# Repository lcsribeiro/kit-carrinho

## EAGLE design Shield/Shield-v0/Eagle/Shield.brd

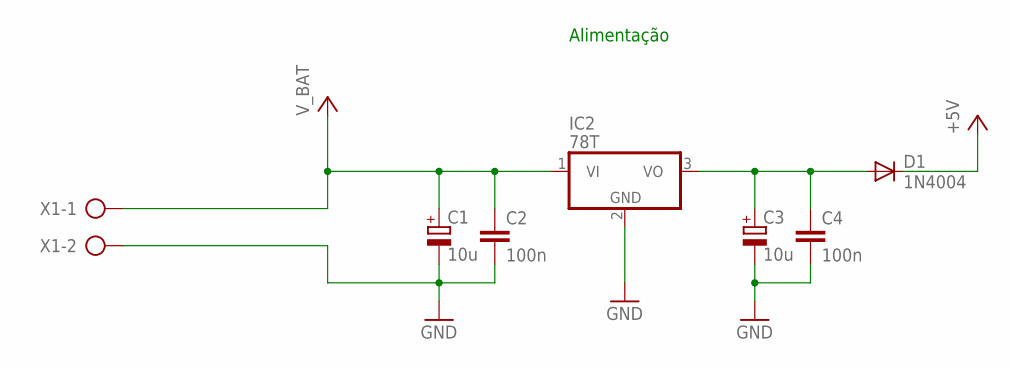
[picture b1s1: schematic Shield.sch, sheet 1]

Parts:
C1, C3: 10u; E2,5-5
C2, C4: 100n; C025-024X044
D1: 1N4004; DO41-10
IC2: 78T; TO220H
X1: AK300/2

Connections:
+5: C3.+, C4.1, D1.A, IC2.3 (VO)
+5V: D1.C; also elsewhere on the board
GND: C1.-, C2.2, C3.-, C4.2, IC2.2 (GND), X1.2; also elsewhere on the board
V_BAT: C1.+, C2.1, IC2.1 (VI), X1.1; also elsewhere on the board

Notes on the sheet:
Alimentação

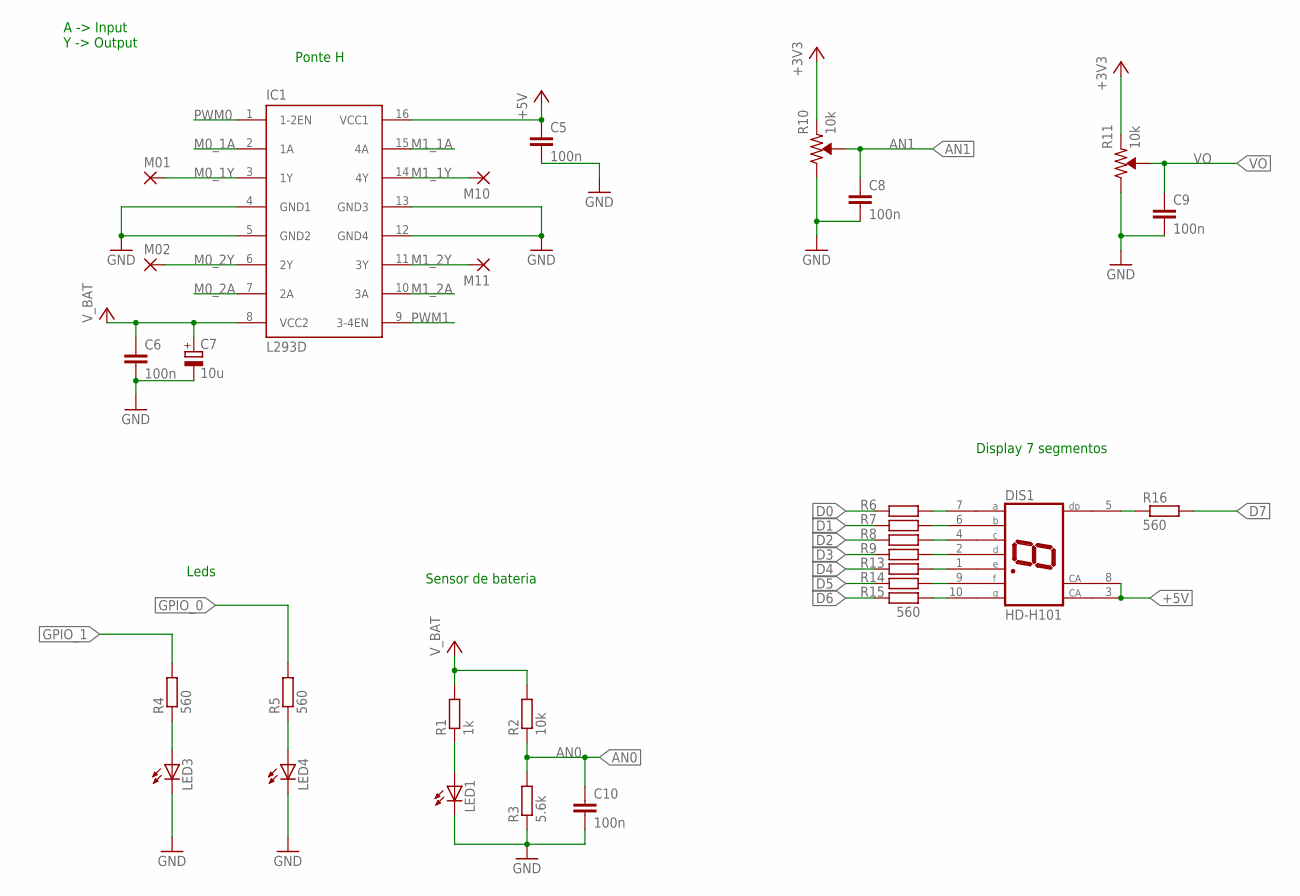
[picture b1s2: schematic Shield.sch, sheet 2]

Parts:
C5, C6, C8, C9, C10: 100n; C025-024X044
C7: 10u; E2,5-5
DIS1: HD-H101; HDSP-M
IC1: L293D; DIL16
LED1, LED3, LED4: LED5MM
M01, M02, M10, M11: 2,54/1,1
R1: 1k; 0204/7
R2: 10k; 0204/7
R3: 5.6k; 0204/7
R4, R5, R6, R7, R8, R9, R13, R14, R15, R16: 560; 0204/7
R10, R11: 10k; TRIMPOT-PTH-3386U

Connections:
+3V3: R10.1 (CCW), R11.1 (CCW); also elsewhere on the board
+5V: C5.1, DIS1.3 (CA), DIS1.8 (CA), IC1.16 (VCC1); also elsewhere on the board
AN0: C10.1, R2.1, R3.2; also elsewhere on the board
AN1: C8.1, R10.2 (WIPER); also elsewhere on the board
D0: R6.1; also elsewhere on the board
D1: R7.1; also elsewhere on the board
D2: R8.1; also elsewhere on the board
D3: R9.1; also elsewhere on the board
D4: R13.1; also elsewhere on the board
D5: R14.1; also elsewhere on the board
D6: R15.1; also elsewhere on the board
D7: R16.2; also elsewhere on the board
GND: C5.2, C6.2, C7.-, C8.2, C9.2, C10.2, IC1.4 (GND1), IC1.5 (GND2), IC1.12 (GND4), IC1.13 (GND3), LED1.K (C), LED3.K (C), LED4.K (C), R3.1, R10.3 (CW), R11.3 (CW); also elsewhere on the board
GPIO_0: R5.2; also elsewhere on the board
GPIO_1: R4.2; also elsewhere on the board
M0_1A: IC1.2 (1A); also elsewhere on the board
M0_1Y: IC1.3 (1Y), M01.1
M0_2A: IC1.7 (2A); also elsewhere on the board
M0_2Y: IC1.6 (2Y), M02.1
M1_1A: IC1.15 (4A); also elsewhere on the board
M1_1Y: IC1.14 (4Y), M10.1
M1_2A: IC1.10 (3A); also elsewhere on the board
M1_2Y: IC1.11 (3Y), M11.1
unnamed: DIS1.7 (A), R6.2
unnamed: LED1.A, R1.1
unnamed: DIS1.6 (B), R7.2
unnamed: DIS1.4 (C), R8.2
unnamed: DIS1.2 (D), R9.2
unnamed: DIS1.1 (E), R13.2
unnamed: DIS1.9 (F), R14.2
unnamed: DIS1.10 (G), R15.2
unnamed: DIS1.5 (DP), R16.1
unnamed: LED3.A, R4.1
unnamed: LED4.A, R5.1
PWM0: IC1.1 (1-2EN); also elsewhere on the board
PWM1: IC1.9 (3-4EN); also elsewhere on the board
VO: C9.1, R11.2 (WIPER); also elsewhere on the board
V_BAT: C6.1, C7.+, IC1.8 (VCC2), R1.2, R2.2; also elsewhere on the board

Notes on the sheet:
A -> Input Y -> Output
Ponte H
Sensor de bateria
Leds
Display 7 segmentos

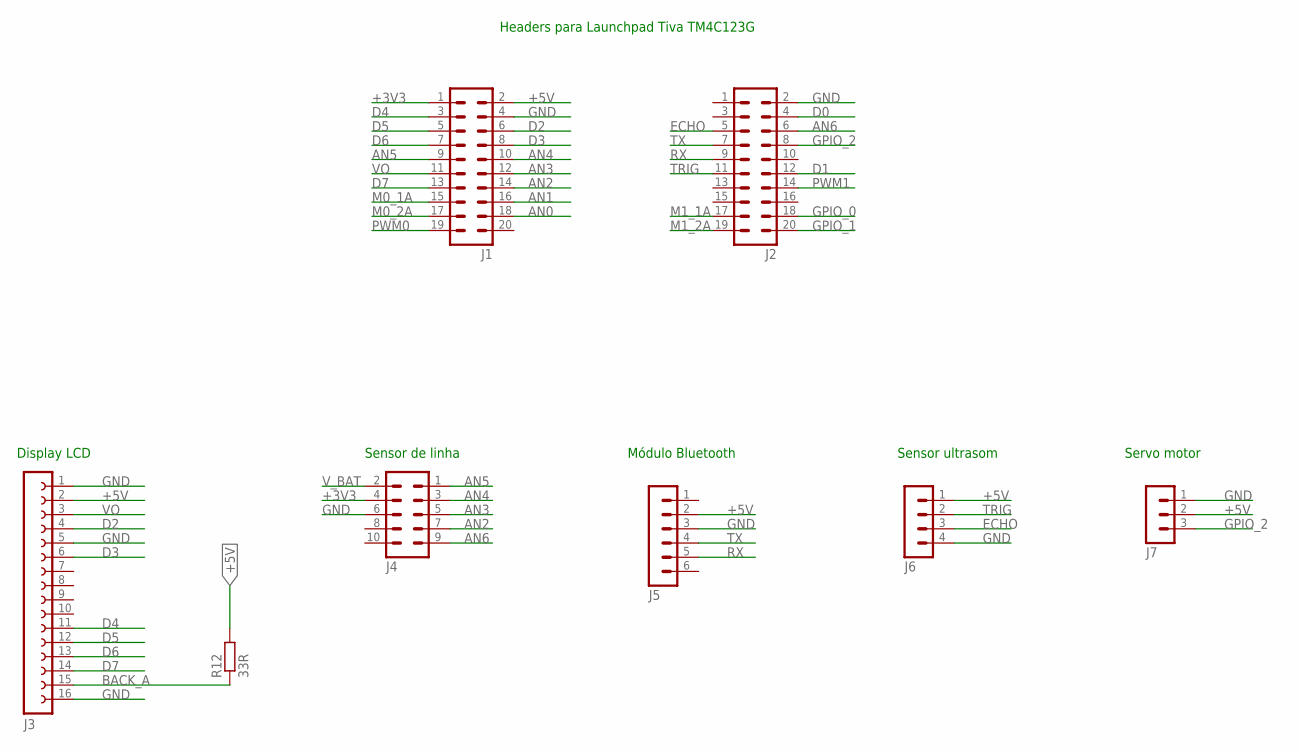
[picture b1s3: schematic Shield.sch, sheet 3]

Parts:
J1, J2: MA10-2
J3: FE16-1; FE16
J4: MA05-2
J5: MA06-1
J6: MA04-1
J7: MA03-1
R12: 33R; 0204/7

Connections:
+3V3: J1.1, J4.4; also elsewhere on the board
+5V: J1.2, J3.2, J5.2, J6.1, J7.2, R12.2; also elsewhere on the board
AN0: J1.18; also elsewhere on the board
AN1: J1.16; also elsewhere on the board
AN2: J1.14, J4.7
AN3: J1.12, J4.5
AN4: J1.10, J4.3
AN5: J1.9, J4.1
AN6: J2.6, J4.9
BACK_A: J3.15, R12.1
D0: J2.4; also elsewhere on the board
D1: J2.12; also elsewhere on the board
D2: J1.6, J3.4; also elsewhere on the board
D3: J1.8, J3.6; also elsewhere on the board
D4: J1.3, J3.11; also elsewhere on the board
D5: J1.5, J3.12; also elsewhere on the board
D6: J1.7, J3.13; also elsewhere on the board
D7: J1.13, J3.14; also elsewhere on the board
ECHO: J2.5, J6.3
GND: J1.4, J2.2, J3.1, J3.5, J3.16, J4.6, J5.3, J6.4, J7.1; also elsewhere on the board
GPIO_0: J2.18; also elsewhere on the board
GPIO_1: J2.20; also elsewhere on the board
GPIO_2: J2.8, J7.3
M0_1A: J1.15; also elsewhere on the board
M0_2A: J1.17; also elsewhere on the board
M1_1A: J2.17; also elsewhere on the board
M1_2A: J2.19; also elsewhere on the board
PWM0: J1.19; also elsewhere on the board
PWM1: J2.14; also elsewhere on the board
RX: J2.9, J5.5
TRIG: J2.11, J6.2
TX: J2.7, J5.4
VO: J1.11, J3.3; also elsewhere on the board
V_BAT: J4.2; also elsewhere on the board

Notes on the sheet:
Sensor ultrasom
Módulo Bluetooth
Sensor de linha
Servo motor
Headers para Launchpad Tiva TM4C123G
Display LCD

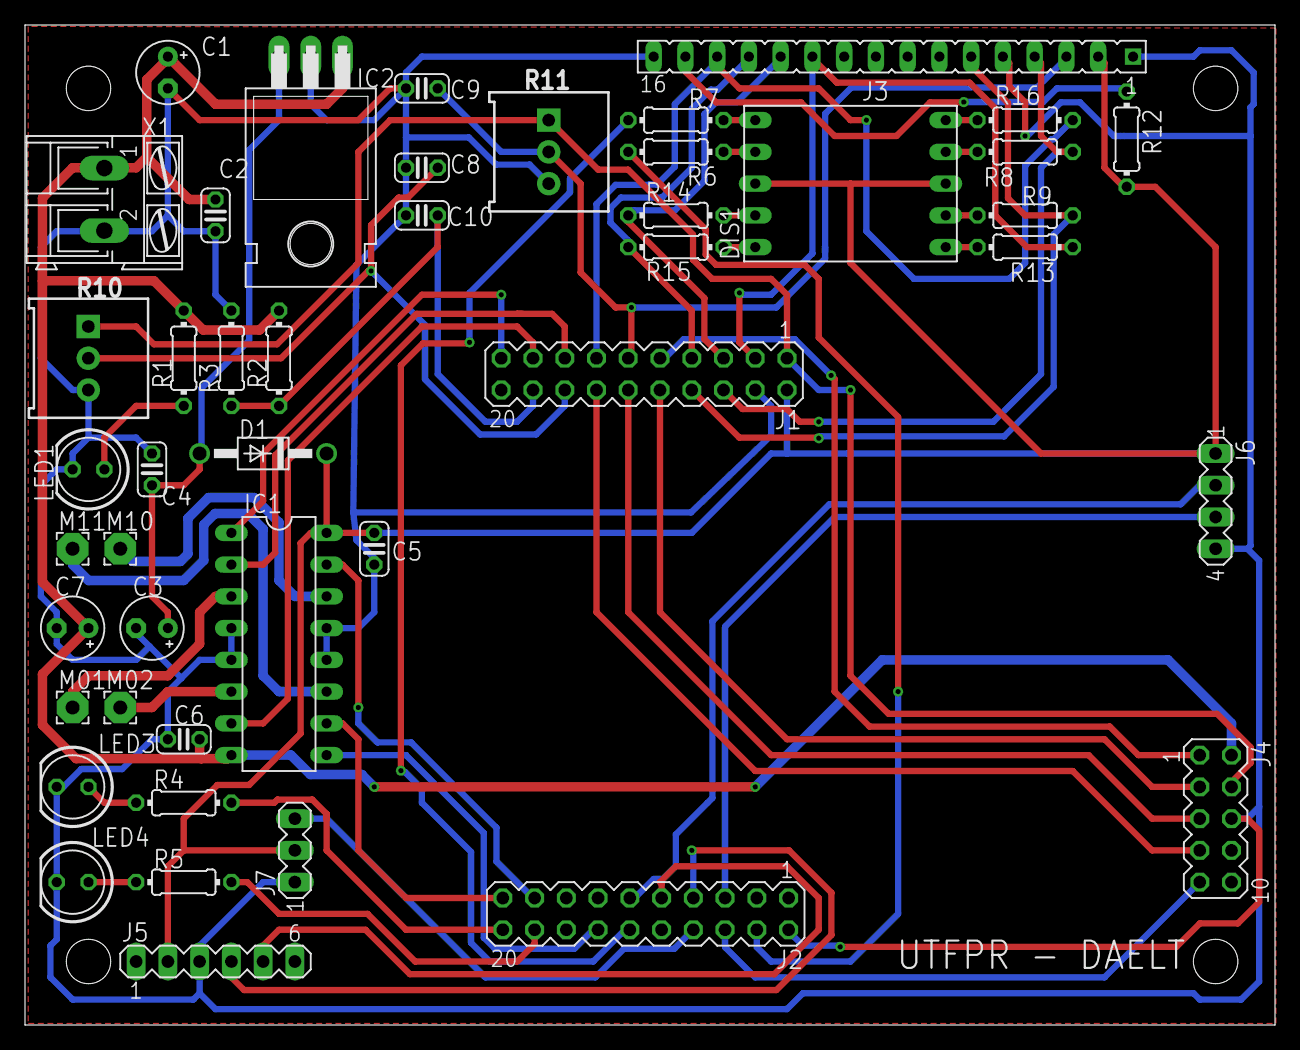
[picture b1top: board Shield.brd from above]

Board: 2 copper layers, 100.0 x 80.0 mm, 45 parts (0 on the bottom side), 50 nets.

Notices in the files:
parts and their libraries:
SparkFun-Resistors: Licensing: Creative Commons ShareAlike 4.0 International - https://creativecommons.org/licenses/by-sa/4.0
